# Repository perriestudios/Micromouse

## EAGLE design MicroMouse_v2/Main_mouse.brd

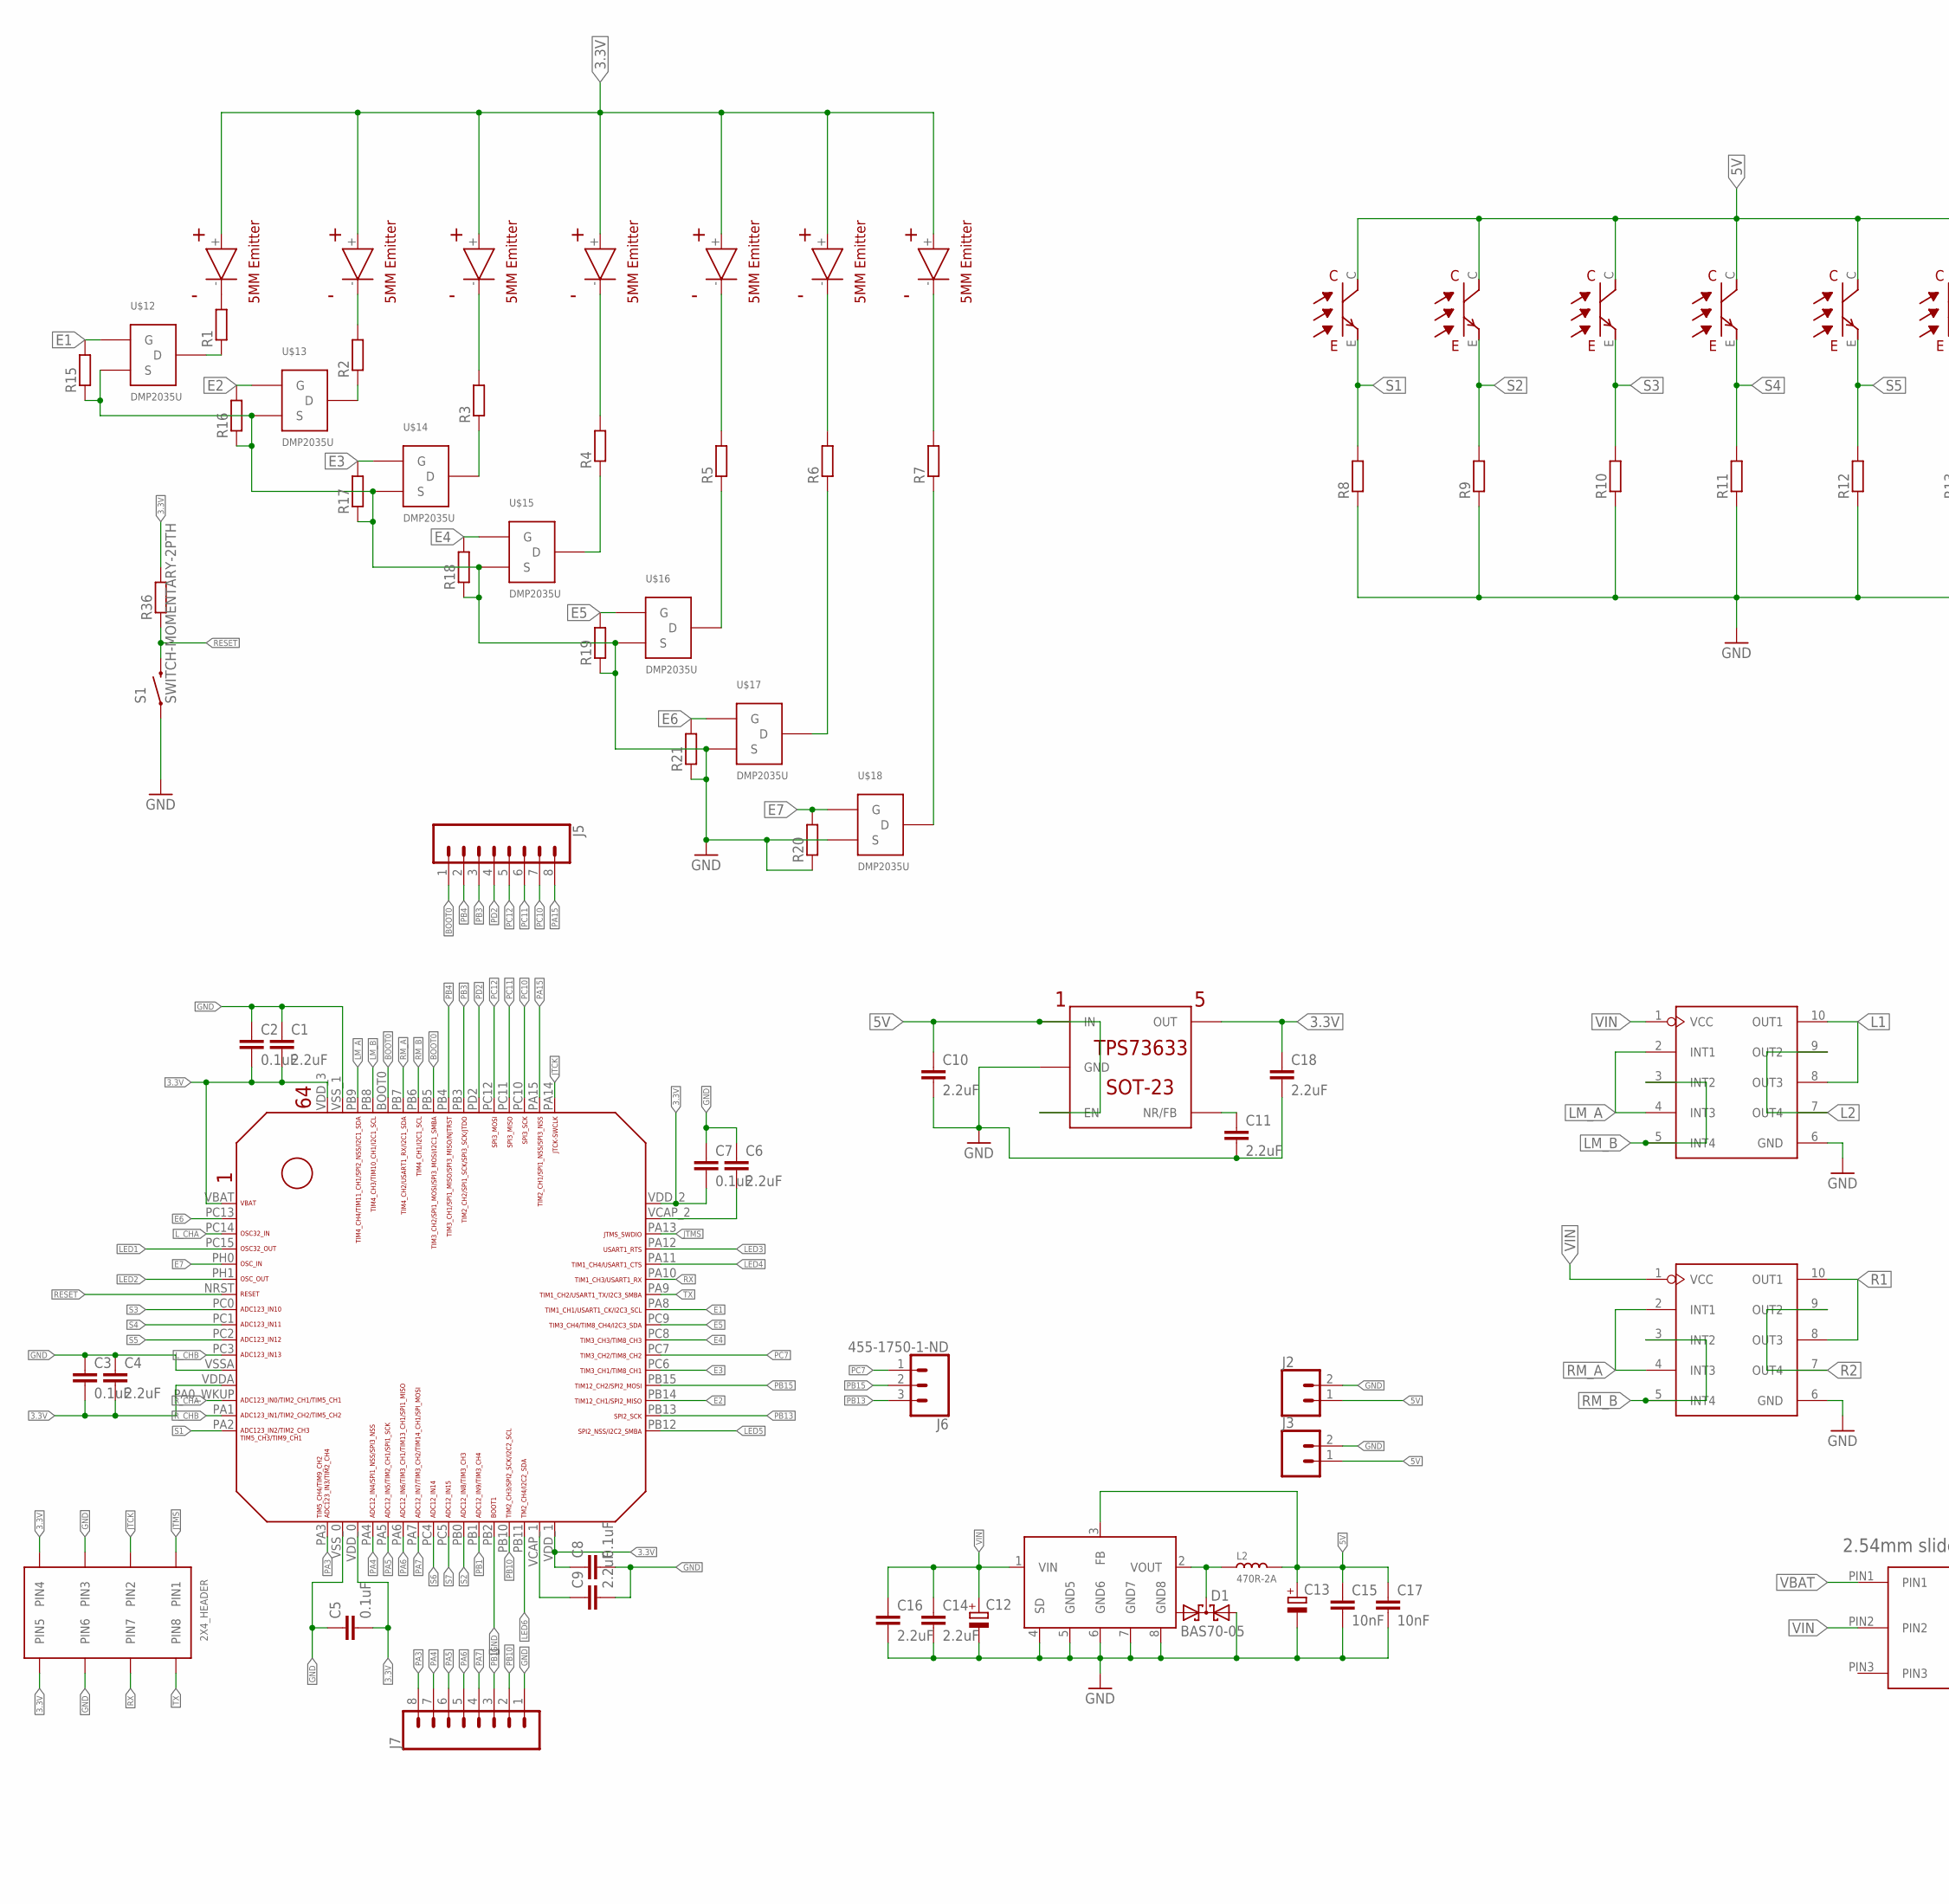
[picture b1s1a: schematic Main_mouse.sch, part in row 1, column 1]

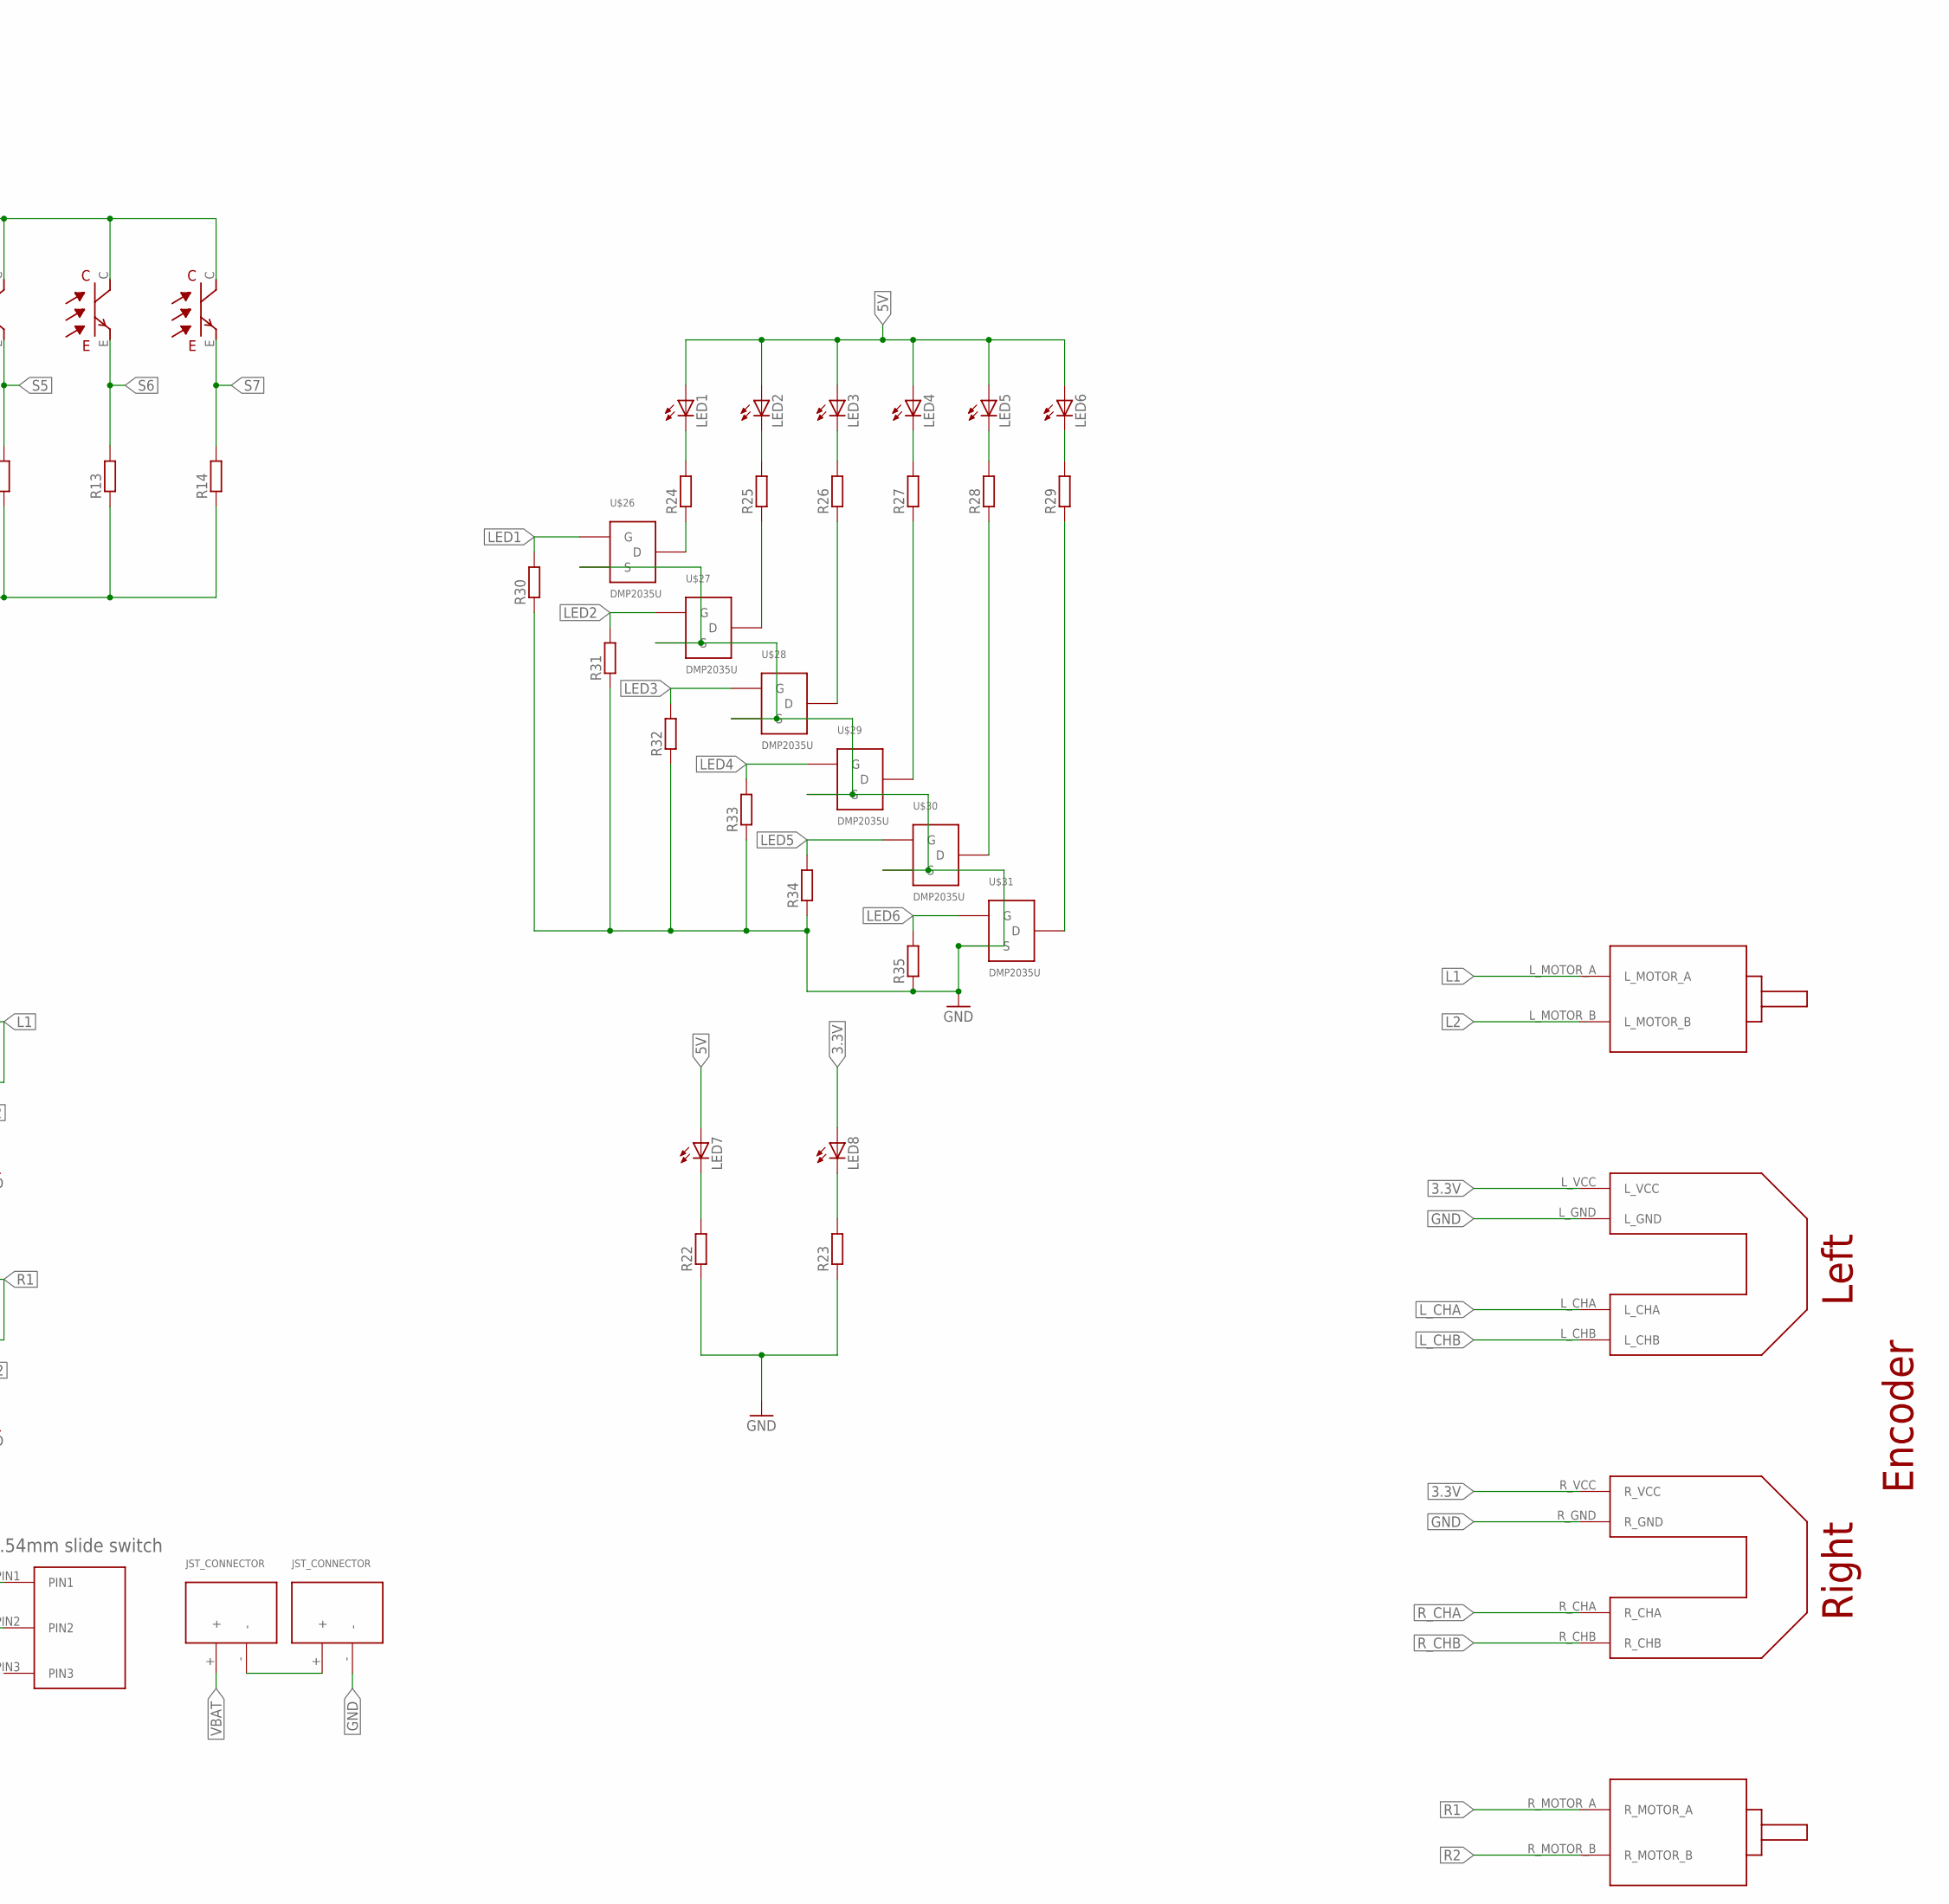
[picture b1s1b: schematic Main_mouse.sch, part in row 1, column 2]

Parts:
C1, C4, C6, C9, C10, C11, C14, C16, C18: 2.2uF; 0603
C2, C3, C5, C7, C8: 0.1uF; 0603
C12: CPOL-EUSMCA; SMC_A
C13: CPOL-EUSMCC; SMC_C
C15, C17: 10nF; 0603
D1: BAS70-05; SOT23
J2, J3: CONN_02PTH3; 1X02_LONGPADS
J5, J7: CONN_08NO_SILK_FEMALE_PTH; 1X08_NO_SILK
J6: 455-1750-1-ND; 1X03
L2: 470R-2A; L0805
LED1, LED2, LED3, LED4, LED5, LED6, LED7, LED8: LEDCHIP-LED0603; CHIP-LED0603
R1, R2, R3, R4, R5, R6, R7, R8, R9, R10, R11, R12, R13, R14, R15, R16, R17, R18, R19, R20, R21, R22, R23, R24, R25, R26, R27, R28, R29, R30, R31, R32, R33, R34, R35, R36: R-EU_R0603; R0603
S1: SWITCH-MOMENTARY-2PTH; TACTILE-PTH
U1, U2: DRIVER-LV8548MC-AH(SOIC10); SOIC10-1.0-5X4MM
U$1: STM32F405/415_LQFP64
U$2: 2X3_HEADER
U$3: AP1509-50SG-13; SO08
U$4: TPS73633(SOT-23)
U$5, U$6, U$7, U$8, U$9, U$10, U$11: EMITTER
U$12, U$13, U$14, U$15, U$16, U$17, U$18, U$26, U$27, U$28, U$29, U$30, U$31: DMP2035U; SOT23
U$19, U$20, U$21, U$22, U$23, U$24, U$25: RECEIVER
U$32: TS02_SWITCH
U$33, U$34: JST_CONNECTOR_FEMALE
U$35: FUTURA_V1.0_MOTOR_MOUNT; FUTURA_V1.0_MOTOT_MOUNT

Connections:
3.3V: C1.2, C2.2, C3.2, C4.2, C5.2, C7.2, C8.1, C18.1, LED8.A, R36.2, U$1.VBAT, U$1.VDDA, U$1.VDD_0, U$1.VDD_1, U$1.VDD_2, U$1.VDD_3, U$2.PIN4, U$2.PIN5, U$4.OUT, U$5.+, U$6.+, U$7.+, U$8.+, U$9.+, U$10.+, U$11.+, U$35.L_VCC, U$35.R_VCC
5V: C10.1, C13.+, C15.1, C17.1, J2.1, J3.1, L2.2, LED1.A, LED2.A, LED3.A, LED4.A, LED5.A, LED6.A, LED7.A, U$3.3 (FB), U$4.EN, U$4.IN, U$19.C, U$20.C, U$21.C, U$22.C, U$23.C, U$24.C, U$25.C
BOOT0: J5.1, U$1.BOOT0, U$1.PB5
E1: R15.2, U$1.PA8, U$12.1 (G)
E2: R16.2, U$1.PB14, U$13.1 (G)
E3: R17.2, U$1.PC6, U$14.1 (G)
E4: R18.2, U$1.PC8, U$15.1 (G)
E5: R19.2, U$1.PC9, U$16.1 (G)
E6: R21.2, U$1.PC13, U$17.1 (G)
E7: R20.2, U$1.PH0, U$18.1 (G)
GND: C1.1, C2.1, C3.1, C4.1, C5.1, C6.1, C7.1, C8.2, C9.2, C10.2, C11.2, C12.-, C13.-, C14.2, C15.2, C16.2, C17.2, C18.2, D1.2 (A2), J2.2, J3.2, J7.1, R8.1, R9.1, R10.1, R11.1, R12.1, R13.1, R14.1, R15.1, R16.1, R17.1, R18.1, R19.1, R20.1, R21.1, R22.1, R23.1, R30.1, R31.1, R32.1, R33.1, R34.1, R35.1, S1.1, U1.6 (GND), U2.6 (GND), U$1.PB2, U$1.VSSA, U$1.VSS_0, U$1.VSS_1, U$2.PIN3, U$2.PIN6, U$3.4 (SD), U$3.5 (GND5), U$3.6 (GND6), U$3.7 (GND7), U$3.8 (GND8), U$4.GND, U$12.2 (S), U$13.2 (S), U$14.2 (S), U$15.2 (S), U$16.2 (S), U$17.2 (S), U$18.2 (S), U$26.2 (S), U$27.2 (S), U$28.2 (S), U$29.2 (S), U$30.2 (S), U$31.2 (S), U$34.-, U$35.L_GND, U$35.R_GND
JTCK: U$1.PA14, U$2.PIN2
JTMS: U$1.PA13, U$2.PIN1
L1: U1.8 (OUT3), U1.10 (OUT1), U$35.L_MOTOR_A
L2: U1.7 (OUT4), U1.9 (OUT2), U$35.L_MOTOR_B
LED1: R30.2, U$1.PC15, U$26.1 (G)
LED2: R31.2, U$1.PH1, U$27.1 (G)
LED3: R32.2, U$1.PA12, U$28.1 (G)
LED4: R33.2, U$1.PA11, U$29.1 (G)
LED5: R34.2, U$1.PB12, U$30.1 (G)
LED6: R35.2, U$1.PB11, U$31.1 (G)
LM_A: U1.2 (INT1), U1.4 (INT3), U$1.PB9
LM_B: U1.3 (INT2), U1.5 (INT4), U$1.PB8
L_CHA: U$1.PC14, U$35.L_CHA
L_CHB: U$1.PC3, U$35.L_CHB
unnamed: C9.1, U$1.VCAP_1
unnamed: C6.2, U$1.VCAP_2
unnamed: R1.1, U$12.3 (D)
unnamed: D1.3 (C), L2.1, U$3.2 (VOUT)
unnamed: C11.1, U$4.NR/FB
unnamed: R2.2, U$6.-
unnamed: R2.1, U$13.3 (D)
unnamed: R4.1, U$15.3 (D)
unnamed: R3.1, U$14.3 (D)
unnamed: R6.1, U$17.3 (D)
unnamed: R3.2, U$7.-
unnamed: R1.2, U$5.-
unnamed: R4.2, U$8.-
unnamed: R5.2, U$9.-
unnamed: R5.1, U$16.3 (D)
unnamed: R6.2, U$10.-
unnamed: R7.1, U$18.3 (D)
unnamed: R7.2, U$11.-
unnamed: LED7.C, R22.2
unnamed: LED8.C, R23.2
unnamed: LED1.C, R24.2
unnamed: LED2.C, R25.2
unnamed: LED3.C, R26.2
unnamed: LED4.C, R27.2
unnamed: LED5.C, R28.2
unnamed: LED6.C, R29.2
unnamed: R24.1, U$26.3 (D)
unnamed: R25.1, U$27.3 (D)
unnamed: R26.1, U$28.3 (D)
unnamed: R27.1, U$29.3 (D)
unnamed: R29.1, U$31.3 (D)
unnamed: R28.1, U$30.3 (D)
unnamed: U$33.-, U$34.+
PA3: J7.8, U$1.PA3
PA4: J7.7, U$1.PA4
PA5: J7.6, U$1.PA5
PA6: J7.5, U$1.PA6
PA7: J7.4, U$1.PA7
PA15: J5.8, U$1.PA15
PB1: J7.3, U$1.PB1
PB3: J5.3, U$1.PB3
PB4: J5.2, U$1.PB4
PB10: J7.2, U$1.PB10
PB13: J6.3, U$1.PB13
PB15: J6.2, U$1.PB15
PC7: J6.1, U$1.PC7
PC10: J5.7, U$1.PC10
PC11: J5.6, U$1.PC11
PC12: J5.5, U$1.PC12
PD2: J5.4, U$1.PD2
R1: U2.8 (OUT3), U2.10 (OUT1), U$35.R_MOTOR_A
R2: U2.7 (OUT4), U2.9 (OUT2), U$35.R_MOTOR_B
RESET: R36.1, S1.3 (2), U$1.NRST
RM_A: U2.2 (INT1), U2.4 (INT3), U$1.PB7
RM_B: U2.3 (INT2), U2.5 (INT4), U$1.PB6
RX: U$1.PA10, U$2.PIN7
R_CHA: U$1.PA0_WKUP (PA0_AKUP), U$35.R_CHA
R_CHB: U$1.PA1, U$35.R_CHB
S1: R8.2, U$1.PA2, U$19.E
S2: R9.2, U$1.PB0, U$20.E
S3: R10.2, U$1.PC0, U$21.E
S4: R11.2, U$1.PC1, U$22.E
S5: R12.2, U$1.PC2, U$23.E
S6: R13.2, U$1.PC4, U$24.E
S7: R14.2, U$1.PC5, U$25.E
TX: U$1.PA9, U$2.PIN8
VBAT: U$32.PIN1, U$33.+
VIN: C12.+, C14.1, C16.1, U1.1 (VCC), U2.1 (VCC), U$3.1 (VIN), U$32.PIN2

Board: 2 copper layers, 107 parts (1 on the bottom side), 93 nets, no tracks yet.

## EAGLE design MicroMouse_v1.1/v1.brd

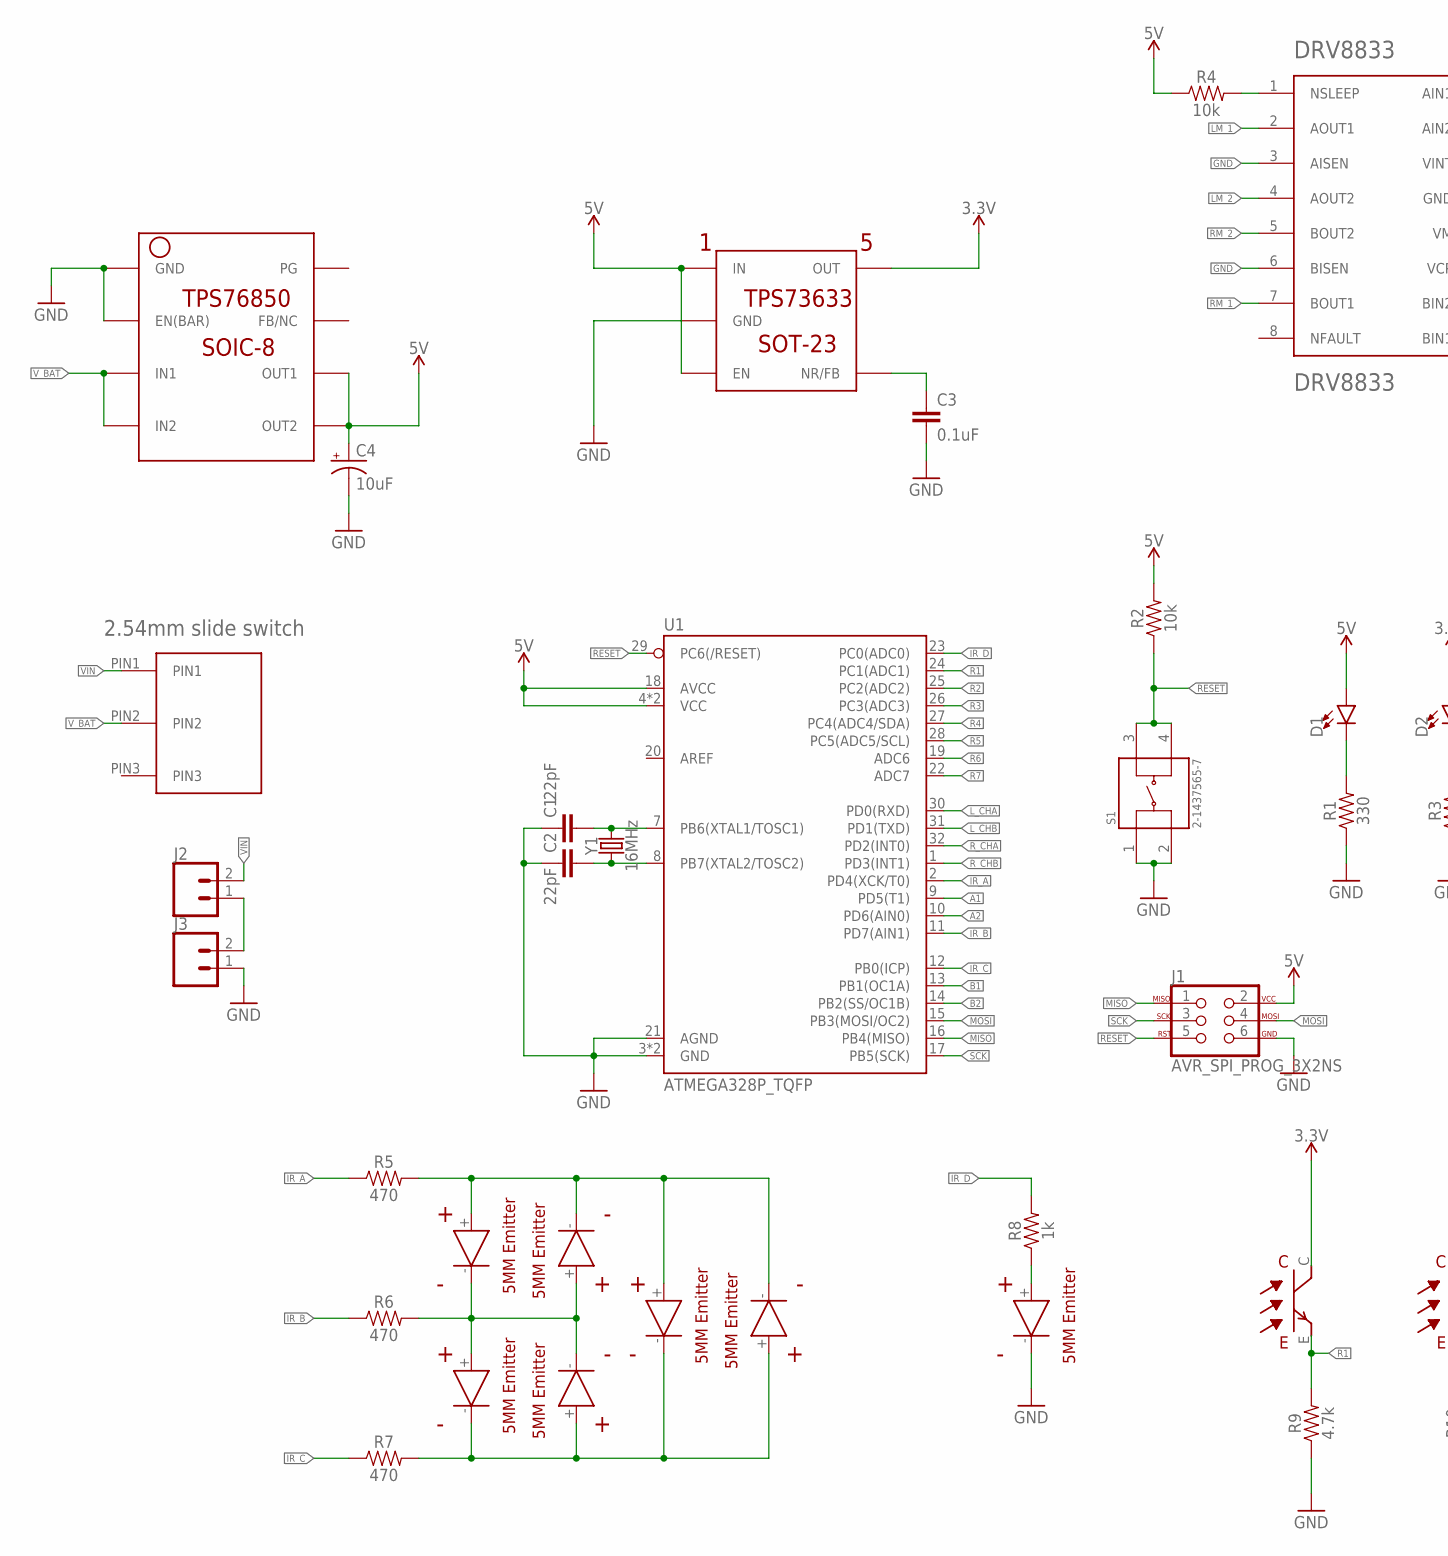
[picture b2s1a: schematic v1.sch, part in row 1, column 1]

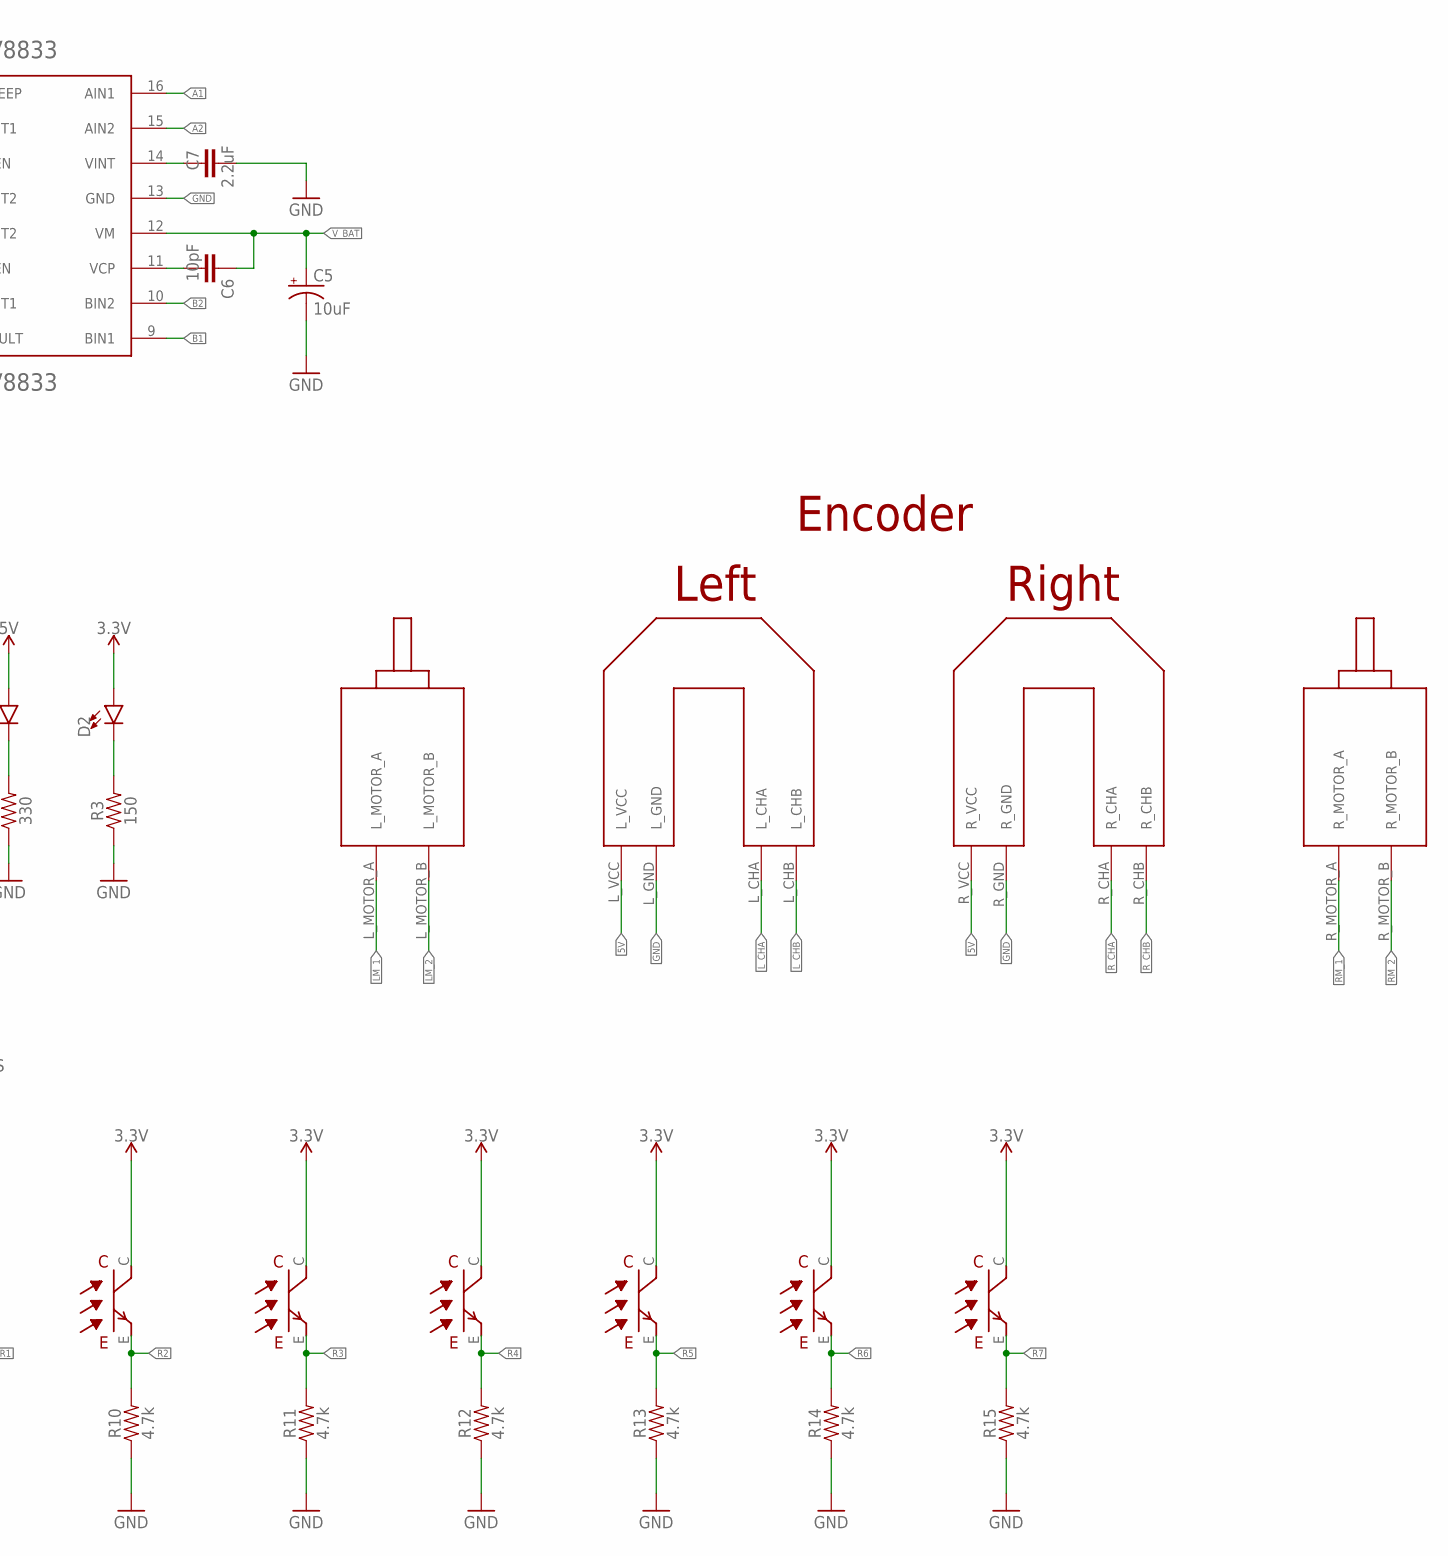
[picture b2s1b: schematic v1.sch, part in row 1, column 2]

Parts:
C1, C2: 22pF; 0603
C3: 0.1uF; 0603
C4, C5: 10uF; EIA3216
C6: 10pF; 0603
C7: 2.2uF; 0603
D1, D2: LED0603; LED-0603
DRV8833PWP1: DRV8833; SOP65P640X120-17N
J1: AVR_SPI_PROG_3X2NS; 2X3-NS
J2, J3: CONN_02; 1X02
R1: 330; 0603
R2, R4: 10k; 0603
R3: 150; 0603
R5, R6, R7: 470; 0603
R8: 1k; 0603
R9, R10, R11, R12, R13, R14, R15: 4.7k; 0603
S1: 2-1437565-7; SW_2-1437565-7
U1: ATMEGA328P_TQFP; TQFP32-08
U$1: TPS73633(SOT-23)
U$2: TPS76850(SOIC-8)
U$3: TS02_SWITCH
U$4: FUTURA_V1.0_MOTOR_MOUNT; FUTURA_V1.0_MOTOT_MOUNT
U$5, U$6, U$7, U$8, U$9, U$10, U$11: EMITTER
U$12, U$13, U$14, U$15, U$16, U$17, U$18: RECEIVER
Y1: 16MHz; HC49US

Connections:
3.3V: D2.A, U$1.OUT, U$12.C, U$13.C, U$14.C, U$15.C, U$16.C, U$17.C, U$18.C
5V: C4.+, D1.A, J1.2, R2.2, R4.1, U1.4 (VCC), U1.6 (VCC), U1.18 (AVCC), U$1.EN, U$1.IN, U$2.OUT1, U$2.OUT2, U$4.L_VCC, U$4.R_VCC
A1: DRV8833PWP1.16 (AIN1), U1.9 (PD5(T1))
A2: DRV8833PWP1.15 (AIN2), U1.10 (PD6(AIN0))
B1: DRV8833PWP1.9 (BIN1), U1.13 (PB1(OC1A))
B2: DRV8833PWP1.10 (BIN2), U1.14 (PB2(SS/OC1B))
GND: C1.1, C2.1, C3.2, C4.-, C5.-, C7.2, DRV8833PWP1.3 (AISEN), DRV8833PWP1.6 (BISEN), DRV8833PWP1.13 (GND), J1.6, J3.1, R1.1, R3.1, R9.1, R10.1, R11.1, R12.1, R13.1, R14.1, R15.1, S1.1, S1.2, U1.3 (GND), U1.5 (GND), U1.21 (AGND), U$1.GND, U$2.EN(BAR), U$2.GND, U$4.L_GND, U$4.R_GND, U$11.-
IR_A: R5.1, U1.2 (PD4(XCK/T0))
IR_B: R6.1, U1.11 (PD7(AIN1))
IR_C: R7.1, U1.12 (PB0(ICP))
IR_D: R8.2, U1.23 (PC0(ADC0))
LM_1: DRV8833PWP1.2 (AOUT1), U$4.L_MOTOR_A
LM_2: DRV8833PWP1.4 (AOUT2), U$4.L_MOTOR_B
L_CHA: U1.30 (PD0(RXD)), U$4.L_CHA
L_CHB: U1.31 (PD1(TXD)), U$4.L_CHB
MISO: J1.1, U1.16 (PB4(MISO))
MOSI: J1.4, U1.15 (PB3(MOSI/OC2))
unnamed: D1.C, R1.2
unnamed: C1.2, U1.7 (PB6(XTAL1/TOSC1)), Y1.2
unnamed: C2.2, U1.8 (PB7(XTAL2/TOSC2)), Y1.1
unnamed: D2.C, R3.2
unnamed: J2.1, J3.2
unnamed: DRV8833PWP1.1 (NSLEEP), R4.2
unnamed: C3.1, U$1.NR/FB
unnamed: R6.2, U$5.-, U$6.+, U$7.+, U$8.-
unnamed: R8.1, U$11.+
unnamed: R5.2, U$5.+, U$7.-, U$9.+, U$10.-
unnamed: R7.2, U$6.-, U$8.+, U$9.-, U$10.+
unnamed: C7.1, DRV8833PWP1.14 (VINT)
unnamed: C6.2, DRV8833PWP1.11 (VCP)
R1: R9.2, U1.24 (PC1(ADC1)), U$12.E
R2: R10.2, U1.25 (PC2(ADC2)), U$13.E
R3: R11.2, U1.26 (PC3(ADC3)), U$14.E
R4: R12.2, U1.27 (PC4(ADC4/SDA)), U$15.E
R5: R13.2, U1.28 (PC5(ADC5/SCL)), U$16.E
R6: R14.2, U1.19 (ADC6), U$17.E
R7: R15.2, U1.22 (ADC7), U$18.E
RESET: J1.5, R2.1, S1.3, S1.4, U1.29 (PC6(/RESET))
RM_1: DRV8833PWP1.7 (BOUT1), U$4.R_MOTOR_A
RM_2: DRV8833PWP1.5 (BOUT2), U$4.R_MOTOR_B
R_CHA: U1.32 (PD2(INT0)), U$4.R_CHA
R_CHB: U1.1 (PD3(INT1)), U$4.R_CHB
SCK: J1.3, U1.17 (PB5(SCK))
VIN: J2.2, U$3.PIN1
V_BAT: C5.+, C6.1, DRV8833PWP1.12 (VM), U$2.IN1, U$2.IN2, U$3.PIN2

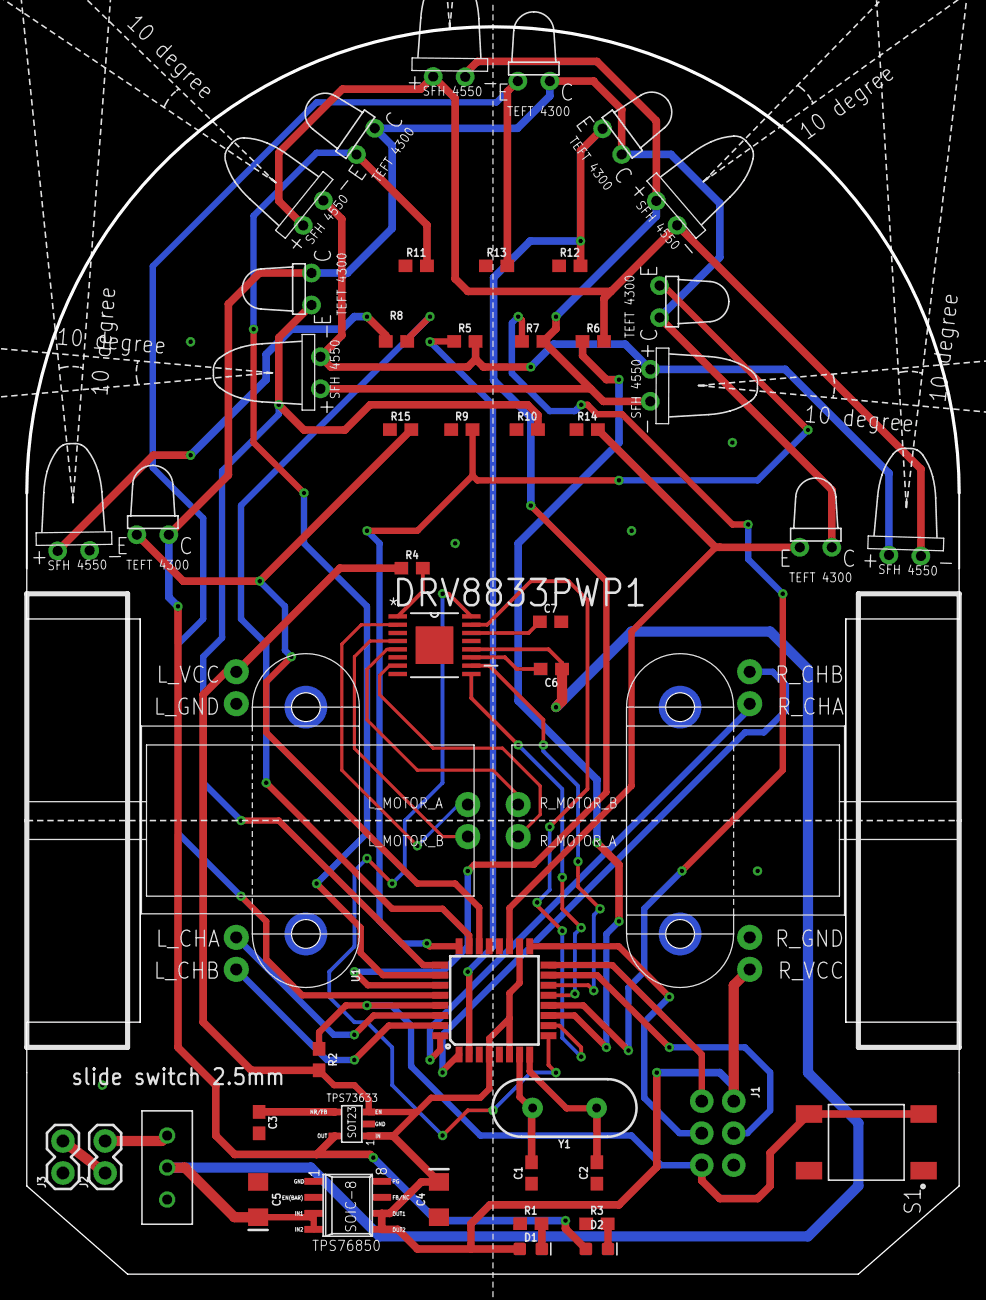
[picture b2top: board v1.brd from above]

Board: 2 copper layers, 74.0 x 98.9 mm, 49 parts (0 on the bottom side), 45 nets.

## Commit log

2020-11-17 Added the files

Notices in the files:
parts and their libraries:
SparkFun-Capacitors: Licensing: Creative Commons ShareAlike 4.0 International - https://creativecommons.org/licenses/by-sa/4.0
SparkFun: Licensing: CC v3.0 Share-Alike You are welcome to use this library for commercial purposes.
